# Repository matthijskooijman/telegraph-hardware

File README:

License
-------
This design is made available under the CERN Open Hardware License,
version 1.2 or above. See LICENSE.txt for the full text of the license.

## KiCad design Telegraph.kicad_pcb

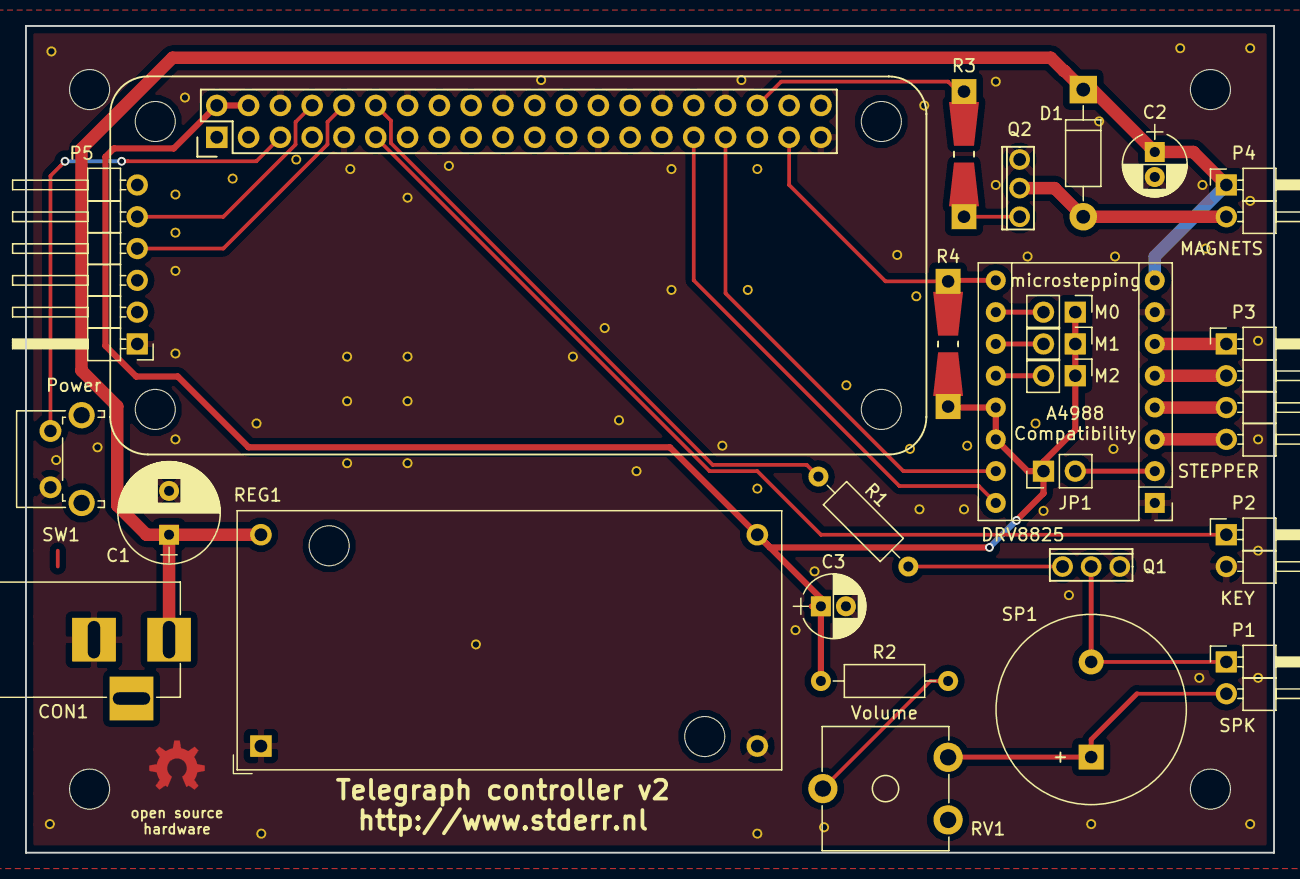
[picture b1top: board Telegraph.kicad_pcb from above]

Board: 2 copper layers, 99.7 x 66.0 mm, 26 parts (0 on the bottom side), 26 nets.

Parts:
A1: Pololu_Breakout_DRV8825; Pololu_Breakout-16_15.2x20.3mm
C1: 470uF; CP_Radial_D8.0mm_P3.50mm
C2, C3: 10uF; CP_Radial_D5.0mm_P2.00mm
CON1: BARREL_JACK
D1: 1N4001; D_DO-41_SOD81_P10.16mm_Horizontal
J1: Raspberry_Pi_2_3; Raspberry_Pi_Zero
JP1: A4988; Pin_Header_Straight_1x02_Pitch2.54mm
JP2: M0; Pin_Header_Straight_1x02_Pitch2.54mm
JP3: M1; Pin_Header_Straight_1x02_Pitch2.54mm
JP4: M2; Pin_Header_Straight_1x02_Pitch2.54mm
P1: SPK; Pin_Header_Angled_1x02_Pitch2.54mm
P2: KEY; Pin_Header_Angled_1x02_Pitch2.54mm
P3: STEPPER; Pin_Header_Angled_1x04_Pitch2.54mm
P4: MAGNETS; Pin_Header_Angled_1x02_Pitch2.54mm
P5: FTDI-DEVICE; Pin_Header_Angled_1x06_Pitch2.54mm
Q1, Q2: STU60N3LH5; TO-251AA
R1: 1K; R_Axial_DIN0207_L6.3mm_D2.5mm_P10.16mm_Horizontal
R2: 12R; R_Axial_DIN0207_L6.3mm_D2.5mm_P10.16mm_Horizontal
R3: 1K; Resistor_SMD+THTuniversal_0805to1206_RM10_HandSoldering
R4: 10K; Resistor_SMD+THTuniversal_0805to1206_RM10_HandSoldering
REG1: REGULATOR_MODULE; HCJ-IPM-V2
RV1: 100R; Potentiometer_Trimmer_ACP_CA9v_Horizontal_Px10.0mm_Py5.0mm
SP1: CVS-1508; Buzzer_15x7.5RM7.6
SW1: SW_Push; SW_Tactile_SPST_Angled_PTS645Vx58-2LFS

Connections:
+5V: A1.13, A1.14, C3.1, J1.2, J1.4, JP1.1, JP2.1, JP3.1, JP4.1, R2.1, R4.1, REG1.4
+12V: A1.8, C1.1, C2.1, CON1.1, D1.1, P4.1, REG1.2
/DIR: A1.16, J1.31
/EN: A1.9, J1.37, R4.2
/KEY: J1.11, P2.1
/MAGNET: J1.36, R3.2
/PWR: J1.5, SW1.2
/RX: J1.10, P5.4
/SPK: J1.12, R1.2
/STEP: A1.15, J1.33
/TX: J1.8, P5.5
GND: A1.1, A1.7, C1.2, C2.2, C3.2, CON1.2, J1.6, J1.9, J1.14, J1.20, J1.25, J1.30, J1.34, J1.39, P2.2, P5.1, Q1.3, Q2.3, REG1.1, REG1.3, SW1.1
unnamed: A1.2, JP1.2
unnamed: A1.3, P3.4
unnamed: A1.4, P3.3
unnamed: A1.5, P3.2
unnamed: A1.6, P3.1
unnamed: A1.10, JP2.2
unnamed: A1.11, JP3.2
unnamed: A1.12, JP4.2
unnamed: D1.2, P4.2, Q2.2
unnamed: P1.1, Q1.2, SP1.2
unnamed: P1.2, RV1.1, SP1.1
unnamed: Q1.1, R1.1
unnamed: Q2.1, R3.1
unnamed: R2.2, RV1.2

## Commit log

2017-07-07 Emtpy initial commit
2017-07-07 Add schematic of first version
    This version was built on experimenter print, so no board layout.
2017-07-08 Bump to v2 and add board layout
    This design is intended for using a Raspberry Pi W and adds a header to
    connect the Raspberry pi directly to the board. This also adds a PCB
    speaker along with a transistor to amplify it, and a switching power
    supply (prefab module). The transistor for the magnets is replaced by a
    MOSFET (which has better specs and mostly a cuter package than the
    TIP12x that was on there).
2017-07-09 Add license notice
2017-07-10 Update plot options for seeed
2017-07-10 Improve values for speaker
    The previous resistor values were more conservative, based on another
    speaker. Testing with the actual speaker, whose type number was also
    addd to the schematic, suggests smaller resistor values will work
    better.
2018-06-25 Convert to KiCad 5
    There might be other changes too, I did not commit this right away...
